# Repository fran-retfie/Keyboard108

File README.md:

# Keyboard108
Another RGB usb-C keyboard with 108 keys

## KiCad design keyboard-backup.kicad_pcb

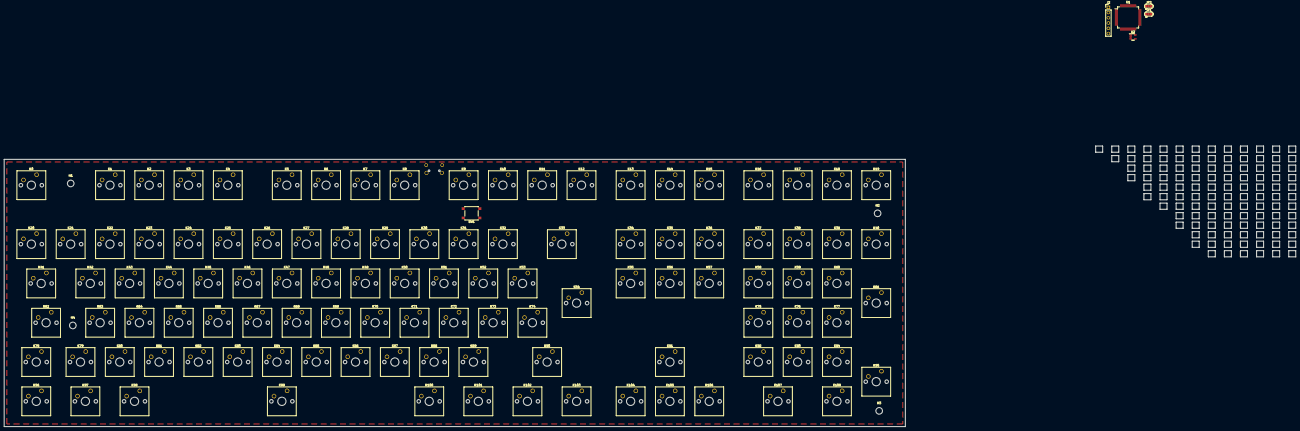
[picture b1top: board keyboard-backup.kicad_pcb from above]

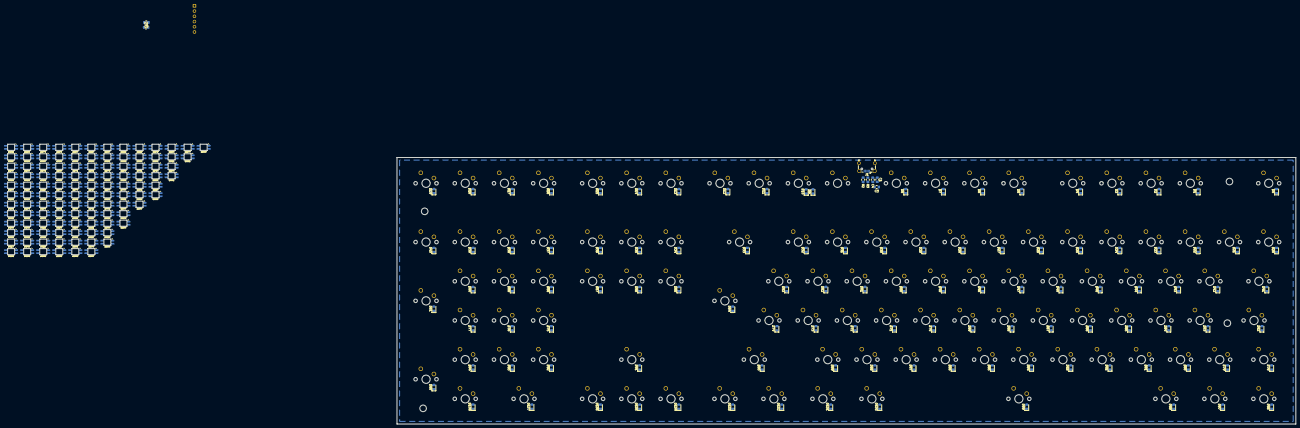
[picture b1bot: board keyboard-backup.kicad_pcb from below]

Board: 2 copper layers, 626.1 x 136.0 mm, 348 parts (229 on the bottom side), 148 nets, no tracks yet.

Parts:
C1, C2, C3, C4: 0.1u; C_0805_2012Metric_Pad1.15x1.40mm_HandSolder
C5: 4.7u; C_0805_2012Metric_Pad1.15x1.40mm_HandSolder
D0, D1, D2, D3, D4, D5, D6, D7, D8, D9, D10, D11, D12, D13, D14, D15, D16, D17, D18, D19, D20, D21, D22, D23, D24, D25, D26, D27, D28, D29, D30, D31, D32, D33, D34, D35, D36, D37, D38, D39, D40, D41, D42, D43, D44, D45, D46, D47, D48, D49, D50, D51, D52, D53, D54, D55, D56, D57, D58, D59, D60, D61, D62, D63, D64, D65, D66, D67, D68, D69, D70, D71, D72, D73, D74, D75, D76, D77, D78, D79, D80, D81, D82, D83, D84, D85, D86, D87, D88, D89, D90, D91, D92, D93, D94, D95, D96, D97, D98, D99, D100, D101, D102, D103, D104, D105, D106, D107, D108: D; D_0805_2012Metric_Pad1.15x1.40mm_HandSolder
D110, D111, D112, D200, D201, D202, D203, D204, D205, D206, D207, D208, D209, D210, D211, D212, D213, D214, D215, D216, D217, D218, D219, D220, D221, D222, D223, D224, D225, D226, D227, D228, D229, D230, D231, D232, D233, D234, D235, D236, D237, D238, D239, D240, D241, D242, D243, D244, D245, D246, D247, D248, D249, D250, D251, D252, D253, D254, D255, D256, D257, D258, D259, D260, D261, D262, D263, D264, D265, D266, D267, D268, D269, D270, D271, D272, D273, D274, D275, D276, D277, D278, D279, D280, D281, D282, D283, D284, D285, D286, D287, D288, D289, D290, D291, D292, D293, D294, D295, D296, D297, D298, D299, D300, D301, D302, D303, D304, D305, D306, D307, D308: SK6812MINI; SK6812-MINI-E
H1, H2, H3, H4: MountingHole; MountingHole_3.2mm_M3_DIN965
J1: USB_B_Micro; USB_Micro-B_Wuerth_629105150521_CircularHoles
J2: Conn_01x06; PinHeader_1x06_P2.54mm_Vertical
JP1, JP2: SolderJumper_3_Open; SolderJumper-3_P1.3mm_Open_RoundedPad1.0x1.5mm
K0, K1, K2, K3, K4, K5, K6, K7, K8, K9, K10, K11, K12, K13, K14, K15, K16, K17, K18, K19, K20, K21, K22, K23, K24, K25, K26, K27, K28, K29, K30, K31, K32, K34, K35, K36, K37, K38, K39, K40, K42, K43, K44, K45, K46, K47, K48, K49, K50, K51, K52, K53, K55, K56, K57, K58, K59, K60, K61, K63, K64, K65, K66, K67, K68, K69, K70, K71, K72, K73, K74, K75, K76, K77, K79, K80, K81, K82, K83, K84, K85, K86, K87, K88, K89, K91, K92, K93, K94, K95, K104, K105, K106, K108: KEYSW; SW_Cherry_MX_1.00u_PCB
K33, K107: KEYSW; SW_Cherry_MX_2.00u_PCB
K41: KEYSW; SW_Cherry_MX_1.50u_PCB
K54, K78, K96, K97, K98, K100, K101, K102, K103: KEYSW; SW_Cherry_MX_1.25u_PCB
K62: KEYSW; SW_Cherry_MX_1.75u_PCB
K90: KEYSW; SW_Cherry_MX_2.75u_PCB
K99: KEYSW; SW_Cherry_MX_6.25u_PCB
R2, R3: 22R; R_0805_2012Metric_Pad1.15x1.40mm_HandSolder
SW1: Reset_SW; SW_Push_1P1T_NO_6x6mm_H9.5mm
U1: STM32F103RBTx; LQFP-64_10x10mm_P0.5mm
U2: MCP1804x-3302xOT; SOT-23-5

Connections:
/Col_0: K0.1, K20.1, K41.1, K62.1, K78.1, K96.1, U1.4 (PC15)
/Col_1: K21.1, K42.1, K63.1, K79.1, K97.1, U1.3 (PC14)
/Col_2: K1.1, K22.1, K43.1, K64.1, K80.1, K98.1, U1.2 (PC13)
/Col_3: K2.1, K23.1, K44.1, K65.1, K81.1, U1.53 (PC12)
/Col_4: K3.1, K24.1, K45.1, K66.1, K82.1, U1.52 (PC11)
/Col_5: K4.1, K25.1, K46.1, K67.1, K83.1, U1.51 (PC10)
/Col_6: K5.1, K26.1, K47.1, K68.1, K84.1, K99.1, U1.40 (PC9)
/Col_7: K6.1, K27.1, K48.1, K69.1, K85.1, U1.39 (PC8)
/Col_8: K7.1, K28.1, K49.1, K70.1, K86.1, U1.38 (PC7)
/Col_9: K8.1, K29.1, K50.1, K71.1, K87.1, U1.37 (PC6)
/Col_10: K9.1, K30.1, K51.1, K72.1, K88.1, K100.1, U1.25 (PC5)
/Col_11: K10.1, K31.1, K52.1, K73.1, K89.1, K101.1, U1.24 (PC4)
/Col_12: K11.1, K32.1, K53.1, K74.1, K102.1, U1.11 (PC3)
/Col_13: K12.1, K33.1, K54.1, K90.1, K103.1, U1.10 (PC2)
/Col_14: K13.1, K34.1, K55.1, K104.1, U1.9 (PC1)
/Col_15: K14.1, K35.1, K56.1, K91.1, K105.1, U1.8 (PC0)
/Col_16: K15.1, K36.1, K57.1, K106.1, U1.54 (PD2)
/Col_17: K16.1, K37.1, K58.1, K75.1, K92.1, K107.1, U1.17 (PA3)
/Col_18: K17.1, K38.1, K59.1, K76.1, K93.1, U1.16 (PA2)
/Col_19: K18.1, K39.1, K60.1, K77.1, K94.1, K108.1, U1.15 (PA1)
/Col_20: K19.1, K40.1, K61.1, K95.1, U1.14 (PA0)
/Reset: J2.3, SW1.2, U1.7 (NRST)
/Row_0: D0.1 (K), D1.1 (K), D2.1 (K), D3.1 (K), D4.1 (K), D5.1 (K), D6.1 (K), D7.1 (K), D8.1 (K), D9.1 (K), D10.1 (K), D11.1 (K), D12.1 (K), D13.1 (K), D14.1 (K), D15.1 (K), D16.1 (K), D17.1 (K), D18.1 (K), D19.1 (K), U1.29 (PB10)
/Row_2: D20.1 (K), D21.1 (K), D22.1 (K), D23.1 (K), D24.1 (K), D25.1 (K), D26.1 (K), D27.1 (K), D28.1 (K), D29.1 (K), D30.1 (K), D31.1 (K), D32.1 (K), D33.1 (K), D34.1 (K), D35.1 (K), D36.1 (K), D37.1 (K), D38.1 (K), D39.1 (K), D40.1 (K), U1.30 (PB11)
/Row_3: D41.1 (K), D42.1 (K), D43.1 (K), D44.1 (K), D45.1 (K), D46.1 (K), D47.1 (K), D48.1 (K), D49.1 (K), D50.1 (K), D51.1 (K), D52.1 (K), D53.1 (K), D54.1 (K), D55.1 (K), D56.1 (K), D57.1 (K), D58.1 (K), D59.1 (K), D60.1 (K), D61.1 (K), U1.33 (PB12)
/Row_4: D62.1 (K), D63.1 (K), D64.1 (K), D65.1 (K), D66.1 (K), D67.1 (K), D68.1 (K), D69.1 (K), D70.1 (K), D71.1 (K), D72.1 (K), D73.1 (K), D74.1 (K), D75.1 (K), D76.1 (K), D77.1 (K), U1.34 (PB13)
/Row_5: D78.1 (K), D79.1 (K), D80.1 (K), D81.1 (K), D82.1 (K), D83.1 (K), D84.1 (K), D85.1 (K), D86.1 (K), D87.1 (K), D88.1 (K), D89.1 (K), D90.1 (K), D91.1 (K), D92.1 (K), D93.1 (K), D94.1 (K), D95.1 (K), U1.35 (PB14)
/Row_6: D96.1 (K), D97.1 (K), D98.1 (K), D99.1 (K), D100.1 (K), D101.1 (K), D102.1 (K), D103.1 (K), D104.1 (K), D105.1 (K), D106.1 (K), D107.1 (K), D108.1 (K), U1.36 (PB15)
/SWCLK: J2.2, U1.49 (PA14)
/SWDIO: J2.1, U1.46 (PA13)
GND: C1.2, C2.2, C3.2, C4.2, C5.2, J1.5 (GND), J1.6 (Shield), J2.4, JP1.1 (A), JP2.3 (B), SW1.1, U1.12 (VSSA), U1.18 (VSS), U1.31 (VSS), U1.47 (VSS), U1.63 (VSS), U2.2 (GND)
unnamed: D0.2 (A), K0.2
unnamed: D1.2 (A), K1.2
unnamed: D2.2 (A), K2.2
unnamed: D3.2 (A), K3.2
unnamed: D4.2 (A), K4.2
unnamed: D5.2 (A), K5.2
unnamed: D6.2 (A), K6.2
unnamed: D7.2 (A), K7.2
unnamed: D8.2 (A), K8.2
unnamed: D9.2 (A), K9.2
unnamed: D10.2 (A), K10.2
unnamed: D11.2 (A), K11.2
unnamed: D12.2 (A), K12.2
unnamed: D13.2 (A), K13.2
unnamed: D14.2 (A), K14.2
unnamed: D15.2 (A), K15.2
unnamed: D16.2 (A), K16.2
unnamed: D17.2 (A), K17.2
unnamed: D18.2 (A), K18.2
unnamed: D19.2 (A), K19.2
unnamed: D20.2 (A), K20.2
unnamed: D21.2 (A), K21.2
unnamed: D22.2 (A), K22.2
unnamed: D23.2 (A), K23.2
unnamed: D24.2 (A), K24.2
unnamed: D25.2 (A), K25.2
unnamed: D26.2 (A), K26.2
unnamed: D27.2 (A), K27.2
unnamed: D28.2 (A), K28.2
unnamed: D29.2 (A), K29.2
unnamed: D30.2 (A), K30.2
unnamed: D31.2 (A), K31.2
unnamed: D32.2 (A), K32.2
unnamed: D33.2 (A), K33.2
unnamed: D34.2 (A), K34.2
unnamed: D35.2 (A), K35.2
unnamed: D36.2 (A), K36.2
unnamed: D37.2 (A), K37.2
unnamed: D38.2 (A), K38.2
unnamed: D39.2 (A), K39.2
unnamed: D40.2 (A), K40.2
unnamed: D41.2 (A), K41.2
unnamed: D42.2 (A), K42.2
unnamed: D43.2 (A), K43.2
unnamed: D44.2 (A), K44.2
unnamed: D45.2 (A), K45.2
unnamed: D46.2 (A), K46.2
unnamed: D47.2 (A), K47.2
unnamed: D48.2 (A), K48.2
unnamed: D49.2 (A), K49.2
unnamed: D50.2 (A), K50.2
unnamed: D51.2 (A), K51.2
unnamed: D52.2 (A), K52.2
unnamed: D53.2 (A), K53.2
unnamed: D54.2 (A), K54.2
unnamed: D55.2 (A), K55.2
unnamed: D56.2 (A), K56.2
unnamed: D57.2 (A), K57.2
unnamed: D58.2 (A), K58.2
unnamed: D59.2 (A), K59.2
unnamed: D60.2 (A), K60.2
unnamed: D61.2 (A), K61.2
unnamed: D62.2 (A), K62.2
unnamed: D63.2 (A), K63.2
unnamed: D64.2 (A), K64.2
unnamed: D65.2 (A), K65.2
unnamed: D66.2 (A), K66.2
unnamed: D67.2 (A), K67.2
unnamed: D68.2 (A), K68.2
unnamed: D69.2 (A), K69.2
unnamed: D70.2 (A), K70.2
unnamed: D71.2 (A), K71.2
unnamed: D72.2 (A), K72.2
unnamed: D73.2 (A), K73.2
unnamed: D74.2 (A), K74.2
unnamed: D75.2 (A), K75.2
unnamed: D76.2 (A), K76.2
unnamed: D77.2 (A), K77.2
unnamed: D78.2 (A), K78.2
unnamed: D79.2 (A), K79.2
unnamed: D80.2 (A), K80.2
unnamed: D81.2 (A), K81.2
unnamed: D82.2 (A), K82.2
unnamed: D83.2 (A), K83.2
unnamed: D84.2 (A), K84.2
unnamed: D85.2 (A), K85.2
unnamed: D86.2 (A), K86.2
unnamed: D87.2 (A), K87.2
unnamed: D88.2 (A), K88.2
unnamed: D89.2 (A), K89.2
unnamed: D90.2 (A), K90.2
unnamed: D91.2 (A), K91.2
unnamed: D92.2 (A), K92.2
unnamed: D93.2 (A), K93.2
unnamed: D94.2 (A), K94.2
unnamed: D95.2 (A), K95.2
unnamed: D96.2 (A), K96.2
unnamed: D97.2 (A), K97.2
unnamed: D98.2 (A), K98.2
unnamed: D99.2 (A), K99.2
unnamed: D100.2 (A), K100.2
unnamed: D101.2 (A), K101.2
unnamed: D102.2 (A), K102.2
unnamed: D103.2 (A), K103.2
unnamed: D104.2 (A), K104.2
unnamed: D105.2 (A), K105.2
unnamed: D106.2 (A), K106.2
unnamed: D107.2 (A), K107.2
unnamed: D108.2 (A), K108.2
unnamed: J1.2 (D-), R3.2
unnamed: J1.3 (D+), R2.2
unnamed: JP1.2 (C), U1.28 (PB2)
unnamed: JP2.2 (C), U1.60 (BOOT0)
unnamed: R2.1, U1.45 (PA12)
unnamed: R3.1, U1.44 (PA11)
VBUS: J1.1 (VBUS), J2.5, U2.1 (VIN), U2.4 (~SHDN)
VCC: C1.1, C2.1, C3.1, C4.1, C5.1, J2.6, JP1.3 (B), JP2.1 (A), U1.1 (VBAT), U1.13 (VDDA), U1.19 (VDD), U1.32 (VDD), U1.48 (VDD), U1.64 (VDD), U2.5 (VOUT)

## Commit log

2022-06-29 added subtree repo
2022-07-01 leds 1
2022-07-04 pcb almost done
2022-07-05 PCB finished
2022-07-05 PCB finished 2
2022-07-06 Added USB cable connector
